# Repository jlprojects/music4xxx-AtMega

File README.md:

# music4xxx
## Hybrid Music 4000 - Midi adapter 

This is an adapter to allow a MIDI keyboard (or other MIDI device) to appear to the Hybrid Music System as a Hybrid Music4000 keyboard. 

The original Music4000 is a fully polyphonic four octave keyboard which connects to the BBC Microcomputer's user port. The keys are only switched, so there is no velocity or aftertouch. However these can be added after the fact in the Music5000 software.

The adapter takes Midi Note-On and Note-Off events and uses eight shift registers to replicate the original Music4000 keyboard matrix. The shift registers are latched automatically by the host BBC Micro's user port. It uses all through-hole parts, so is easy to build, and as the BBC Micro's userport is handled using hardware, the code on the microcontroller is simplified.. The ATMega328 microcontroller is programmed using the Arduino environment. A simple 3d printed enclosure is provided.

## Resources

* Retro-kit's archive of information of the original Music 4000 keyboard, including manuals and brochures: https://www.retro-kit.co.uk/page.cfm/content/Hybrid-Music-4000-Keyboard/

* Here's the Stardot thread about this project: https://stardot.org.uk/forums/viewtopic.php?f=3&t=16895

* The Stardot 8bit hardware forum often has posts about the Hybrid Music system: https://stardot.org.uk/forums/viewforum.php?f=3

## Other options

There are a couple of independently developed alternatives:

* Hideaway Studio's commercially available adapter: http://www.hideawaystudio.net/ details: https://stardot.org.uk/forums/viewtopic.php?f=3&t=16893

* Daniel J's open source STM32 and Blue Pill based solutions: Github: https://github.com/drdpj/MidiKeyboardBluePill Stardot thread: https://stardot.org.uk/forums/viewtopic.php?f=3&t=17146

## Licence

Unless otherwise marked, work in this repository is licenced under [Creative Commons Attribution-ShareAlike 4.0 International License](http://creativecommons.org/licenses/by-sa/4.0/)

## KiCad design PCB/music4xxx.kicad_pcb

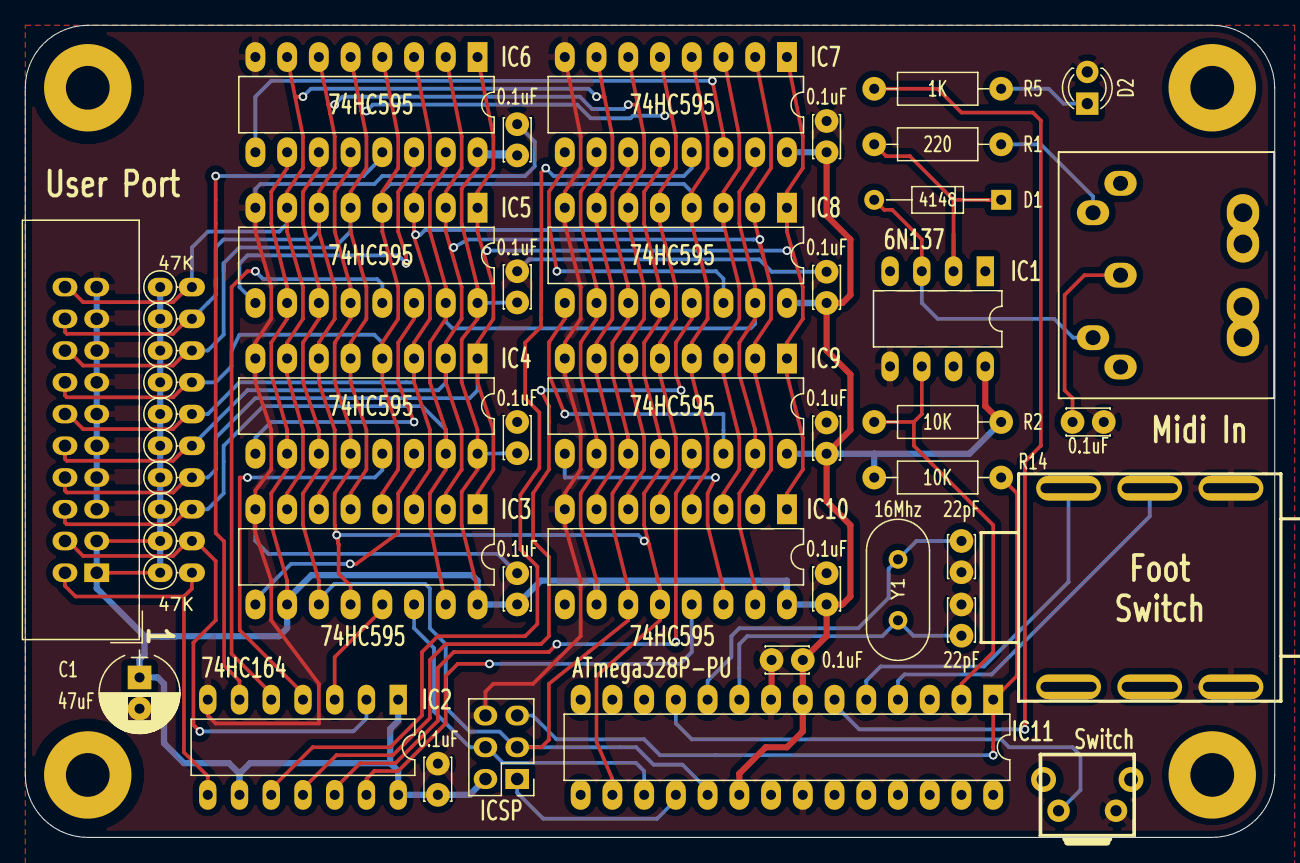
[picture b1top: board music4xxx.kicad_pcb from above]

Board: 2 copper layers, 100.0 x 65.0 mm, 51 parts (0 on the bottom side), 44 nets.

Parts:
C1: 47uF; CP_Radial_D6.3mm_P2.50mm
C2, C3, C4, C5, C6, C7, C8, C9, C10, C11, C12: 0.1uF; C_Disc_D3.4mm_W2.1mm_P2.50mm
C13, C14: 22pF; C_Disc_D3.4mm_W2.1mm_P2.50mm
D1: 4148; D_DO-35_SOD27_P10.16mm_Horizontal
D2: LED; LED_D3.0mm
H1, H2, H3, H4: MountingHole; MountingHole_3.5mm_Pad
IC1: 6N137; DIP-8_W7.62mm_LongPads
IC2: 74HC164; DIP-14_W7.62mm_LongPads
IC3, IC4, IC5, IC6, IC7, IC8, IC9, IC10: 74HC595; DIP-16_W7.62mm_LongPads
IC11: ATmega328P-PU; DIP-28_W7.62mm
J1: IN; din_5_pcb_mount
J2: User Port; IDC-Header_2x10_Pitch2.54mm_Straight
J3: Footswitch; Neutrik-NMJ6HF-S
P1: ICSP; Pin_Header_Straight_2x03_Pitch2.54mm
R1: 220; R_Axial_DIN0207_L6.3mm_D2.5mm_P10.16mm_Horizontal
R2, R14: 10K; R_Axial_DIN0207_L6.3mm_D2.5mm_P10.16mm_Horizontal
R3, R4, R6, R7, R8, R9, R10, R11, R12, R13: 47K; R_Axial_DIN0207_L6.3mm_D2.5mm_P2.54mm_Vertical
R5: 1K; R_Axial_DIN0207_L6.3mm_D2.5mm_P10.16mm_Horizontal
SW1: Panic; VerticalTactSwitch
Y1: 16Mhz; Crystal_HC49-U_Vertical

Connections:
+5V: C1.1, C2.1, C3.1, C5.1, C6.1, C7.1, C8.1, C9.1, C10.1, C11.1, C12.1, IC1.8, IC2.1, IC2.9, IC2.14, IC3.10, IC3.16, IC4.10, IC4.16, IC5.10, IC5.16, IC6.10, IC6.16, IC7.10, IC7.16, IC8.10, IC8.16, IC9.10, IC9.16, IC10.10, IC10.16, IC11.7, IC11.20, J2.1, J2.3, P1.2, R2.2, R3.1, R4.1, R6.1, R7.1, R8.1, R9.1, R10.1, R11.1, R12.1, R13.1, R14.2
/CB1: IC2.8, J2.2, R3.2
/CB2: IC2.2, J2.4, R4.2
/FS1: IC11.5, J3.6
/FS2: IC11.4, J3.5
/MISO: IC11.18, P1.1
/MOSI: IC3.14, IC11.17, P1.4
/OE0: IC2.3, IC3.13
/OE1: IC2.4, IC4.13
/OE2: IC2.5, IC5.13
/OE3: IC2.6, IC6.13
/OE4: IC2.10, IC7.13
/OE5: IC2.11, IC8.13
/OE6: IC2.12, IC9.13
/OE7: IC2.13, IC10.13
/PB0: IC3.15, IC4.15, IC5.15, IC6.15, IC7.15, IC8.15, IC9.15, IC10.15, J2.6, R6.2
/PB1: IC3.1, IC4.1, IC5.1, IC6.1, IC7.1, IC8.1, IC9.1, IC10.1, J2.8, R7.2
/PB2: IC3.2, IC4.2, IC5.2, IC6.2, IC7.2, IC8.2, IC9.2, IC10.2, J2.10, R8.2
/PB3: IC3.3, IC4.3, IC5.3, IC6.3, IC7.3, IC8.3, IC9.3, IC10.3, J2.12, R9.2
/PB4: IC3.4, IC4.4, IC5.4, IC6.4, IC7.4, IC8.4, IC9.4, IC10.4, J2.14, R10.2
/PB5: IC3.5, IC4.5, IC5.5, IC6.5, IC7.5, IC8.5, IC9.5, IC10.5, J2.16, R11.2
/PB6: IC3.6, IC4.6, IC5.6, IC6.6, IC7.6, IC8.6, IC9.6, IC10.6, J2.18, R12.2
/PB7: IC3.7, IC4.7, IC5.7, IC6.7, IC7.7, IC8.7, IC9.7, IC10.7, J2.20, R13.2
/RST: IC11.1, P1.5, R14.1
/RX: IC1.6, IC11.2, R2.1
/SCK: IC3.11, IC4.11, IC5.11, IC6.11, IC7.11, IC8.11, IC9.11, IC10.11, IC11.19, P1.3
/SRlatch: IC3.12, IC4.12, IC5.12, IC6.12, IC7.12, IC8.12, IC9.12, IC10.12, IC11.16
GND: C1.2, C2.2, C3.2, C4.2, C5.2, C6.2, C7.2, C8.2, C9.2, C10.2, C11.2, C12.2, C13.1, C14.1, D2.1, IC1.5, IC2.7, IC3.8, IC4.8, IC5.8, IC6.8, IC7.8, IC8.8, IC9.8, IC10.8, IC11.8, IC11.22, J2.5, J2.7, J2.9, J2.11, J2.13, J2.15, J2.17, J2.19, J3.1, J3.4, P1.6, SW1.1
unnamed: C4.1, J1.2
unnamed: C13.2, IC11.9, Y1.1
unnamed: C14.2, IC11.10, Y1.2
unnamed: D1.1, IC1.2, R1.1
unnamed: D1.2, IC1.3, J1.5
unnamed: D2.2, R5.1
unnamed: IC3.9, IC4.14
unnamed: IC4.9, IC5.14
unnamed: IC5.9, IC6.14
unnamed: IC6.9, IC7.14
unnamed: IC7.9, IC8.14
unnamed: IC8.9, IC9.14
unnamed: IC9.9, IC10.14
unnamed: IC11.6, R5.2
unnamed: IC11.11, SW1.2
unnamed: J1.4, R1.2
